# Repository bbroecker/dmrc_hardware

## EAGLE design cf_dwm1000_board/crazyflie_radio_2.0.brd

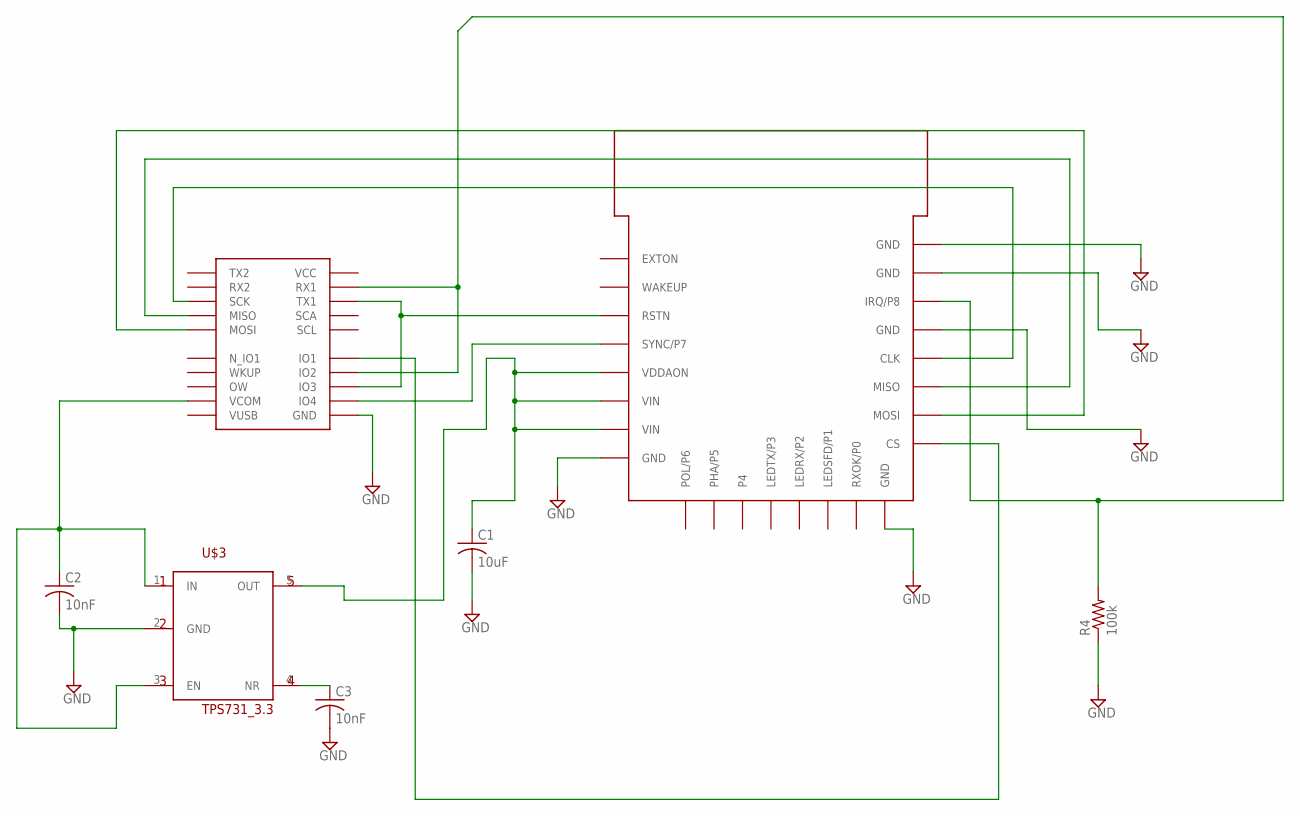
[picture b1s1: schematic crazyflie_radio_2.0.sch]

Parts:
C1: 10uF; C0402
C2, C3: 10nF; C0402
R4: 100k; R0402
U$1: DWM100; DWMPAC
U$2: CFHEAD; CFHEADPAC
U$3: TPS731_3.3; SOT-23-5

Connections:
GND: C1.2, C2.2, C3.2, R4.1, U$1.GND@1 (GND), U$1.GND@2 (GND), U$1.GND@3 (GND), U$1.GND@4 (GND), U$1.GND@5 (GND), U$2.GND, U$3.2 (GND)
unnamed: U$1.SYNC/P7, U$2.IO4
unnamed: U$1.MISO, U$2.MISO
unnamed: U$1.MOSI, U$2.MOSI
unnamed: U$1.CLK, U$2.SCK
unnamed: C2.1, U$2.VCOM, U$3.1 (IN), U$3.3 (EN)
unnamed: U$1.CS, U$2.IO1
unnamed: U$1.RSTN, U$2.IO3, U$2.TX1
unnamed: R4.2, U$1.IRQ/P8, U$2.IO2, U$2.RX1
unnamed: C1.1, U$1.VDDAON, U$1.VIN@1 (VIN), U$1.VIN@2 (VIN), U$3.5 (OUT)
unnamed: C3.1, U$3.4 (NR)

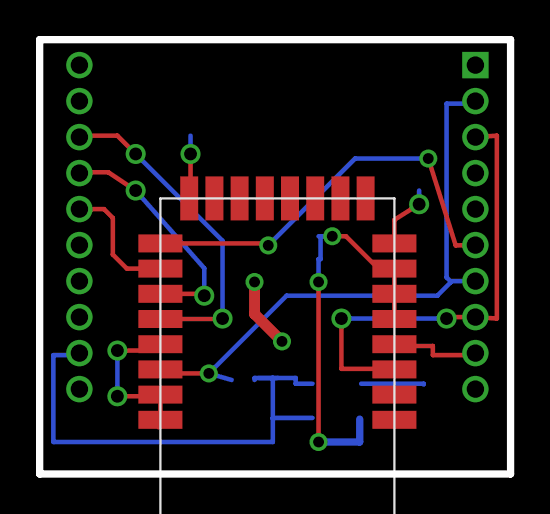
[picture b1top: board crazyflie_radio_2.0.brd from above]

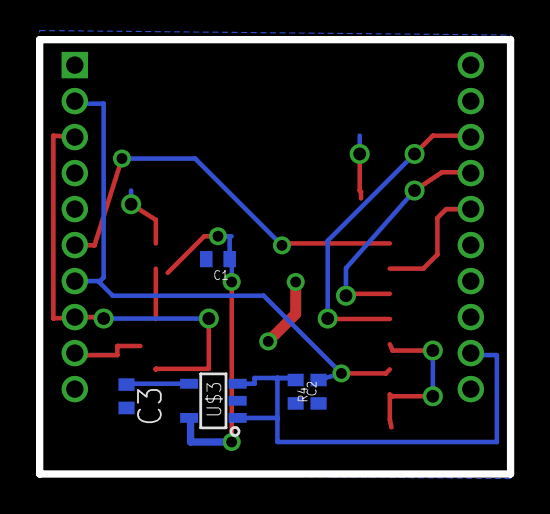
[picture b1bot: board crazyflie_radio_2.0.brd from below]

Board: 2 copper layers, 26.2 x 24.1 mm, 7 parts (5 on the bottom side), 11 nets.

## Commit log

2018-06-24 dwm1000 cf board
